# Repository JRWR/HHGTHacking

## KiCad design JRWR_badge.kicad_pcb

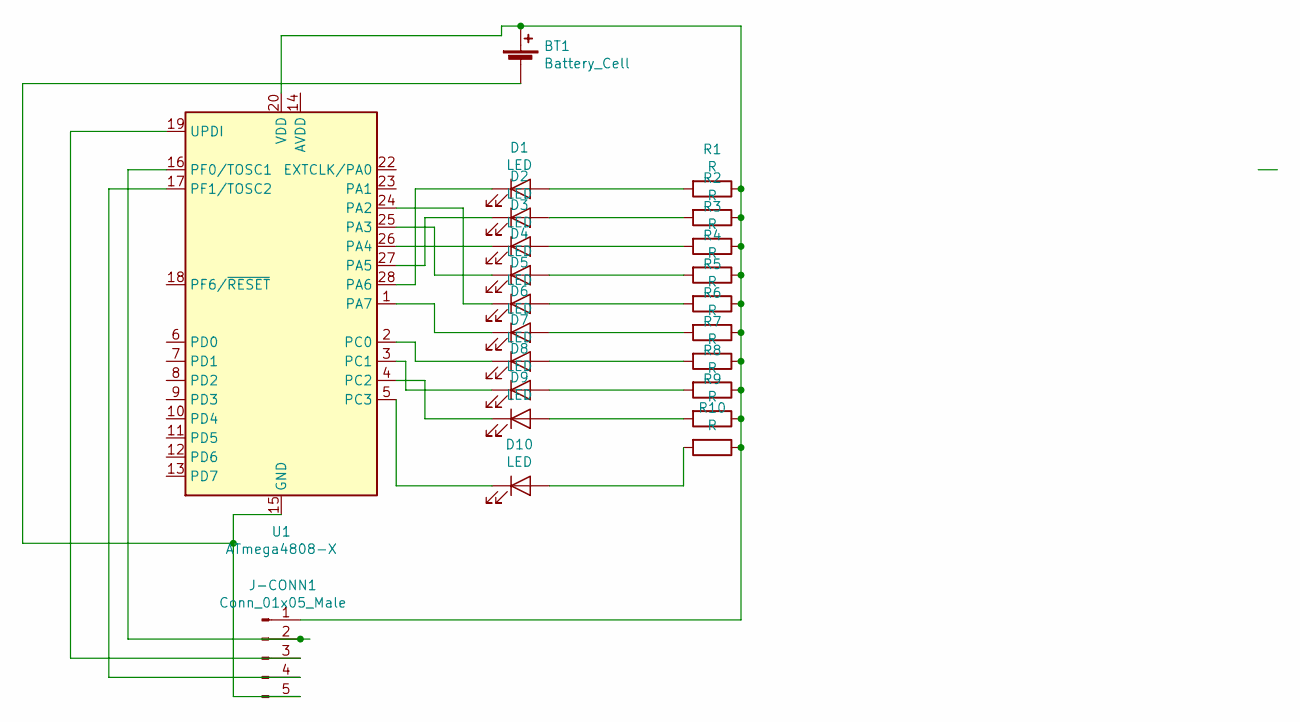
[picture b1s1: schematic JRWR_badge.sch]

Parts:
BT1: Battery_Cell; BatteryHolder_Keystone_3034_1x20mm
D1, D2, D3, D4, D5, D6, D7, D8, D9, D10: LED; LED_0603_1608Metric_Castellated
J-CONN1: Conn_01x05_Male; PinHeader_1x05_P2.54mm_Vertical_SMD_Pin1Left
R1, R2, R3, R4, R5, R6, R7, R8, R9, R10: R; R_0805_2012Metric_Pad1.15x1.40mm_HandSolder
U1: ATmega4808-X; SSOP-28_5.3x10.2mm_P0.65mm

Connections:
unnamed: BT1.1 (+), J-CONN1.1, R1.1, R2.1, R3.1, R4.1, R5.1, R6.1, R7.1, R8.1, R9.1, R10.1, U1.20 (VDD)
unnamed: BT1.2 (-), J-CONN1.5, U1.15 (GND), U1.21 (GND)
unnamed: D1.1 (K), U1.28 (PA6)
unnamed: D1.2 (A), R1.2
unnamed: D2.1 (K), U1.27 (PA5)
unnamed: D2.2 (A), R2.2
unnamed: D3.1 (K), U1.26 (PA4)
unnamed: D3.2 (A), R3.2
unnamed: D4.1 (K), U1.25 (PA3)
unnamed: D4.2 (A), R4.2
unnamed: D5.1 (K), U1.24 (PA2)
unnamed: D5.2 (A), R5.2
unnamed: D6.1 (K), U1.1 (PA7)
unnamed: D6.2 (A), R6.2
unnamed: D7.1 (K), U1.2 (PC0)
unnamed: D7.2 (A), R7.2
unnamed: D8.1 (K), U1.3 (PC1)
unnamed: D8.2 (A), R8.2
unnamed: D9.1 (K), U1.4 (PC2)
unnamed: D9.2 (A), R9.2
unnamed: D10.1 (K), U1.5 (PC3)
unnamed: D10.2 (A), R10.2
unnamed: J-CONN1.2, U1.16 (PF0/TOSC1)
unnamed: J-CONN1.3, U1.19 (UPDI)
unnamed: J-CONN1.4, U1.17 (PF1/TOSC2)

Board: 2 copper layers, 27 parts (23 on the bottom side), 25 nets, no tracks yet.

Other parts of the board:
DNP: TestPoint_Plated_Hole_D5.0mm
G1, G2, G3: LOGO
